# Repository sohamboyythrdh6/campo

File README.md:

# campo
hey i am soham and i build this project for saftey reasons like it detected those spy cameras which recording us without our permeation and i build those project using  a microcontroller called raspberry pico and some photo diode and ir led  i use a custom pcb to build this project 
This project detects hidden cameras using IR light. The photodiode continuously reads the surrounding light and the system first checks the normal light level when it starts. Then it compares new readings with this normal value, and if the value suddenly increases, it means there is a strong reflection which may come from a camera lens. When this happens, the device triggers a buzzer and shows “DETECTED” on the OLED display.

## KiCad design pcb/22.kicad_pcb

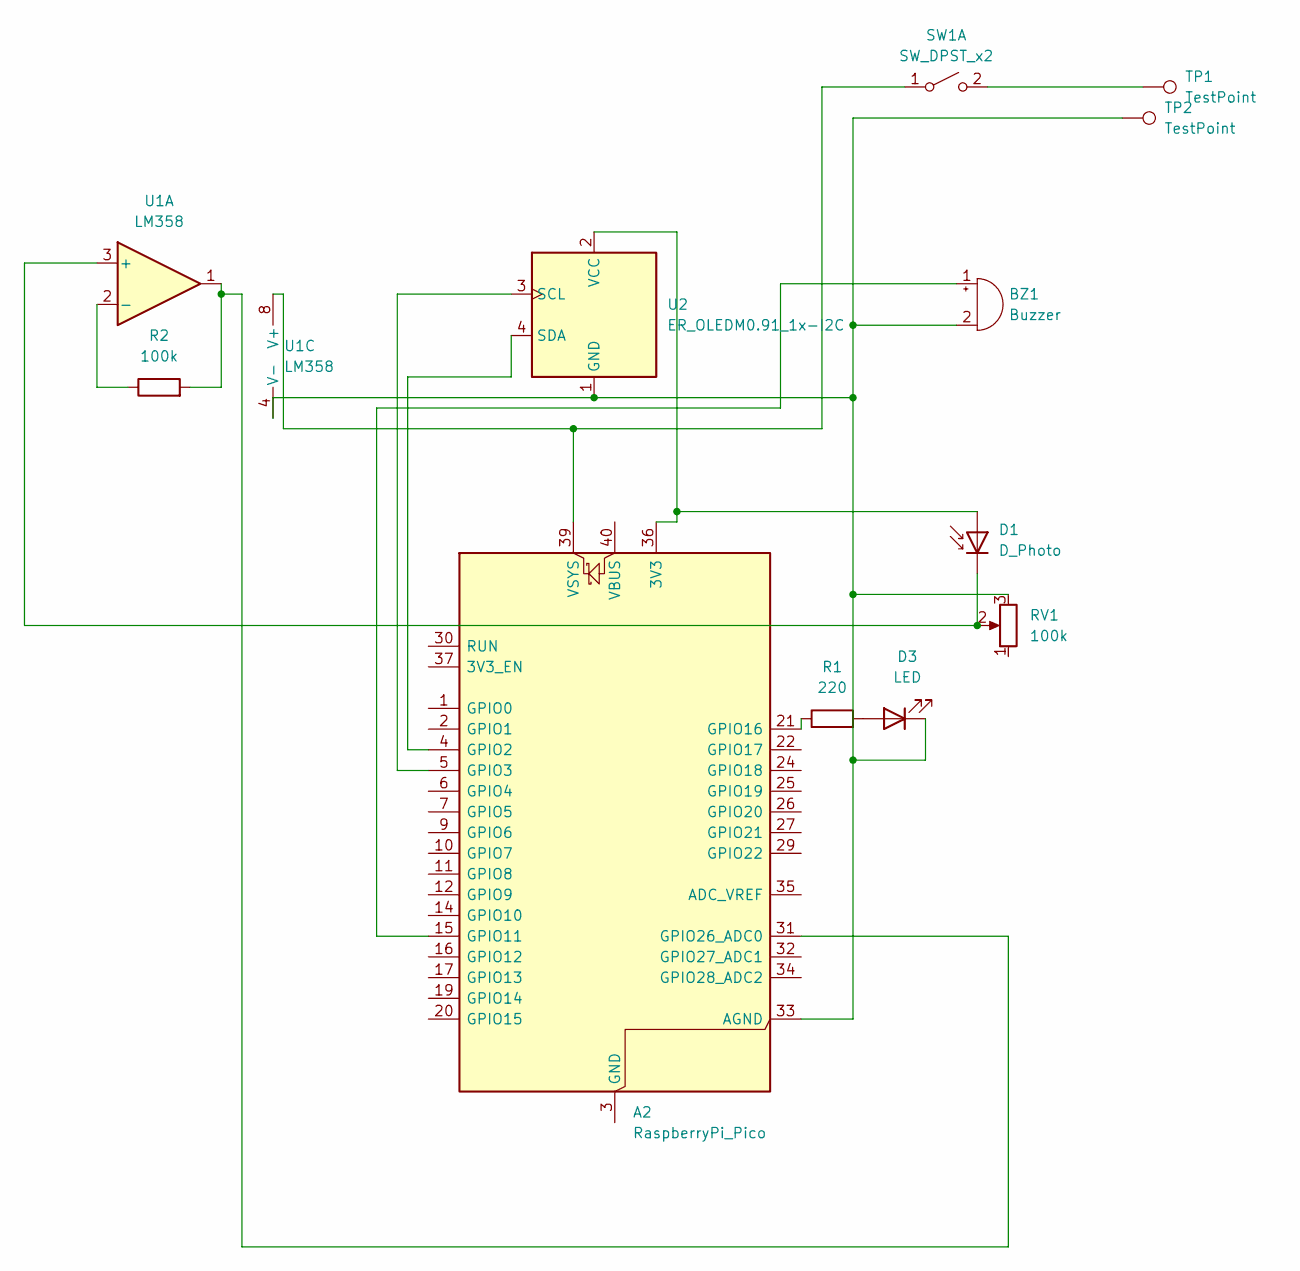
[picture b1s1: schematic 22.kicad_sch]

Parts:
A2: RaspberryPi_Pico; RaspberryPi_Pico_Common_Unspecified
BZ1: Buzzer; Buzzer_12x9.5RM7.6
D1: D_Photo; LED_D5.0mm
D3: LED; LED_D5.0mm
R1: 220; R_Axial_DIN0204_L3.6mm_D1.6mm_P5.08mm_Horizontal
R2: 100k; R_Axial_DIN0204_L3.6mm_D1.6mm_P5.08mm_Horizontal
RV1: 100k; Potentiometer_Bourns_3296W_Vertical
SW1: SW_DPST_x2; SW_CK_JS202011CQN_DPDT_Straight
TP1, TP2: TestPoint; TestPoint_THTPad_1.5x1.5mm_Drill0.7mm
U1: LM358; DIP-8_W7.62mm_Socket
U2: ER_OLEDM0.91_1x-I2C

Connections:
unnamed: A2.36 (3V3), D1.2 (A), U2.2 (VCC)
unnamed: A2.33 (AGND), BZ1.2 (-), D3.1 (K), RV1.3, TP2.1 (1_1), U1.4 (V-), U2.1 (GND)
unnamed: A2.3 (GND), A2.8 (GND), A2.13 (GND), A2.18 (GND), A2.23 (GND), A2.28 (GND), A2.38 (GND)
unnamed: A2.4 (GPIO2), U2.4 (SDA)
unnamed: A2.5 (GPIO3), U2.3 (SCL)
unnamed: A2.15 (GPIO11), BZ1.1 (+)
unnamed: A2.21 (GPIO16), R1.1
unnamed: A2.31 (GPIO26_ADC0), R2.2, U1.1
unnamed: A2.39 (VSYS), SW1.1 (A), U1.8 (V+)
unnamed: D1.1 (K), RV1.2, U1.3 (+)
unnamed: D3.2 (A), R1.2
unnamed: SW1.2 (B), TP1.1 (1_1)
unnamed: R2.1, U1.2 (-)

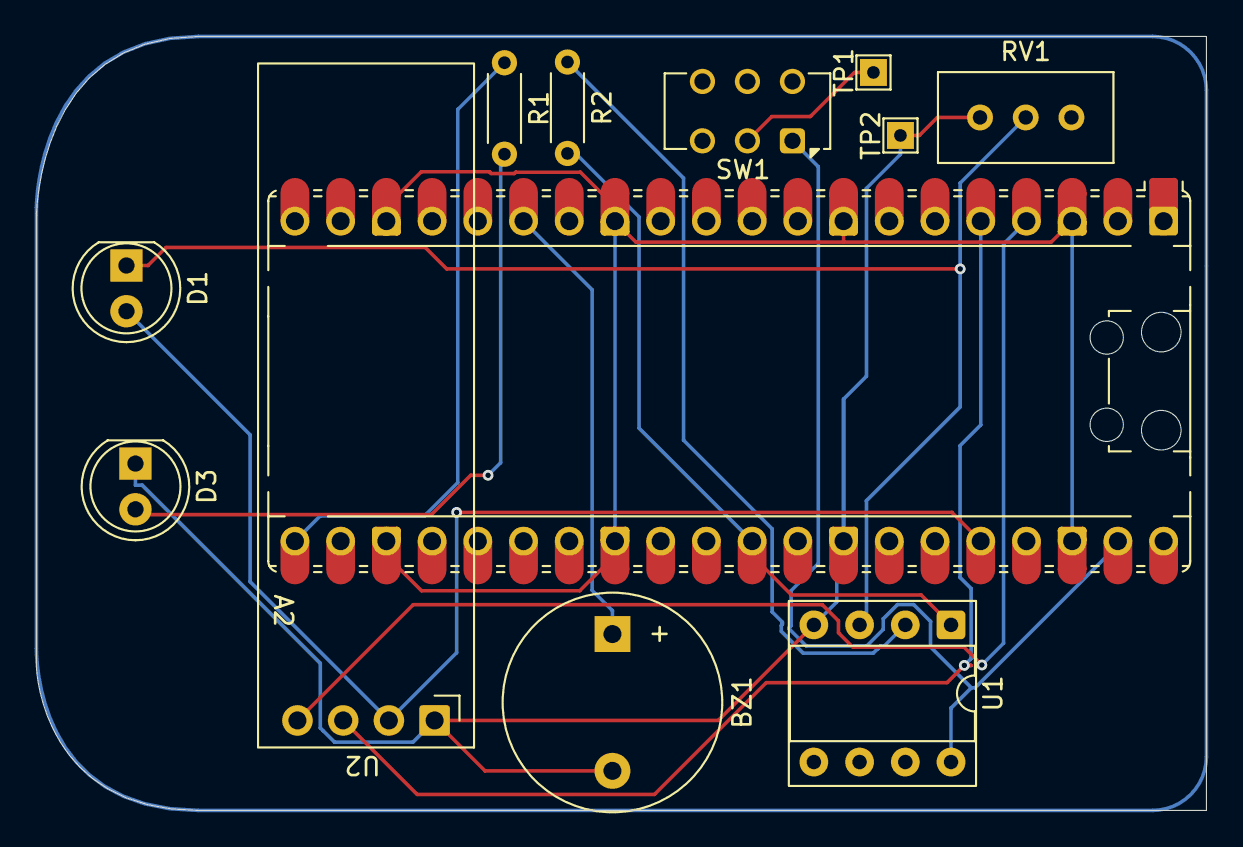
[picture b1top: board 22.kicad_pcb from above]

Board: 2 copper layers, 65.0 x 43.0 mm, 12 parts (0 on the bottom side), 13 nets.

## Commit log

2026-04-22 Create BOM
2026-04-22 Create 7
2026-04-22 Create 4
2026-04-22 Create code
2026-04-22 Rename BOM to BOM.csv
2026-04-22 Rename code to Firmware
2026-04-23 Create Poster
2026-04-23 Update BOM.csv to include product links
    Added links to product details for each item in the BOM.
